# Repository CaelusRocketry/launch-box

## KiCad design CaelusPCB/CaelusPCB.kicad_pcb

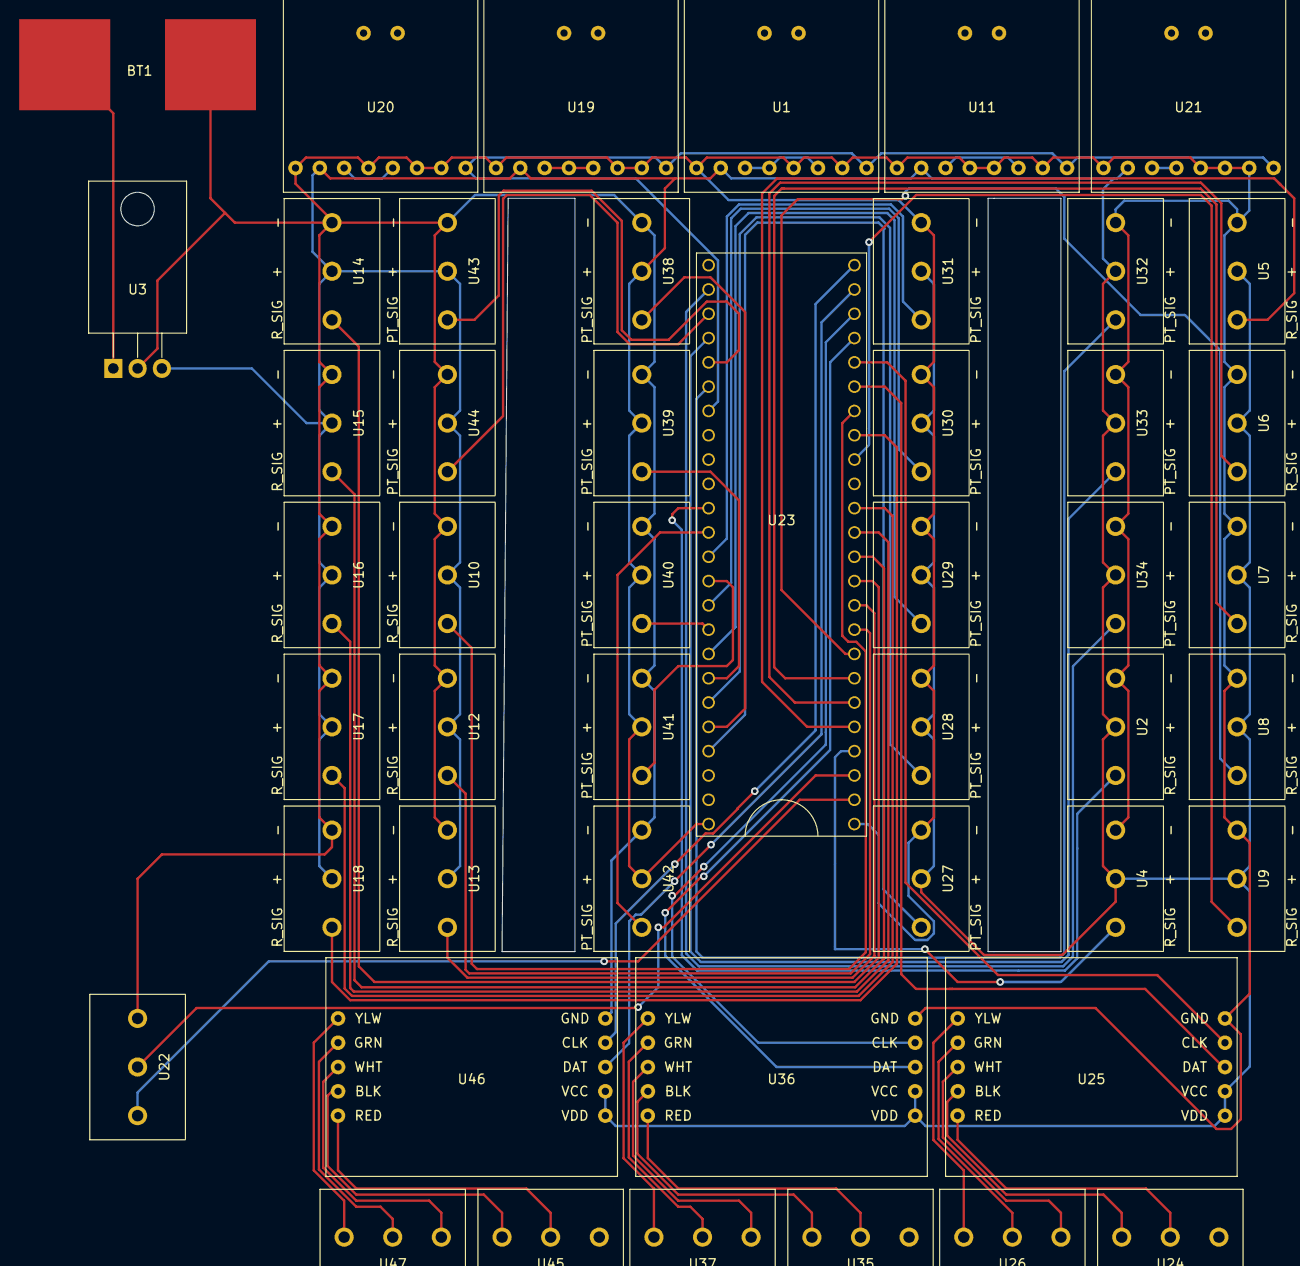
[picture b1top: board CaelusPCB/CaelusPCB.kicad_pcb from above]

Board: 2 copper layers, 48 parts (0 on the bottom side), 62 nets.

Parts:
BT1: Battery_Cell; Lipo_Battery_Connector
U1, U11, U19, U20, U21: MAX31850
U2, U4, U5, U6, U7, U8, U9, U10, U12, U13, U14, U15, U16, U17, U18, U22, U24, U26, U27, U28, U29, U30, U31, U32, U33, U34, U35, U37, U38, U39, U40, U41, U42, U43, U44, U45, U47: SerialScrewTerminals; ScrewTerminals
U3: L7805; TO-220-3_Horizontal_TabDown
U23: Teensy3.6; Teensy 3.6
U25, U36, U46: LoadCellAmp

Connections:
1: U2.1, U23.13
2: U4.1, U23.2
3: U5.1, U23.3
4: U6.1, U23.4
5: U7.1, U23.5
6: U8.1, U23.6
7: U12.1, U23.7
8: U13.1, U23.8
9: U14.1, U23.9
10: U15.1, U23.10
11: U16.1, U23.11
12: U17.1, U23.12
13: U9.1, U23.24
14: U18.1, U23.25
15: U10.1, U23.26
16: U23.27, U25.8
17: U23.28, U25.7
18: U23.29, U36.8
19: U23.30, U36.7
20: U23.31, U46.8
21: U23.32, U46.7
22: U1.8, U11.8, U19.8, U20.8, U21.8, U23.39
23: U22.1, U23.0
24: U22.2, U23.1
+5V: U1.2, U2.2, U3.3, U4.2, U5.2, U6.2, U7.2, U8.2, U9.2, U10.2, U11.2, U12.2, U13.2, U14.2, U15.2, U16.2, U17.2, U18.2, U19.2, U20.2, U21.2, U23.40, U25.9, U25.10, U27.2, U28.2, U29.2, U30.2, U31.2, U32.2, U33.2, U34.2, U36.9, U36.10, U38.2, U39.2, U40.2, U41.2, U42.2, U43.2, U44.2, U46.9, U46.10
GND1: BT1.2, U1.1, U1.5, U1.7, U2.3, U3.2, U4.3, U5.3, U6.3, U7.3, U8.3, U9.3, U10.3, U11.1, U11.4, U11.5, U11.7, U12.3, U13.3, U14.3, U15.3, U16.3, U17.3, U18.3, U19.1, U19.6, U19.7, U20.1, U20.4, U20.6, U20.7, U21.1, U21.5, U21.6, U21.7, U22.3, U23.46, U25.6, U27.3, U28.3, U29.3, U30.3, U31.3, U32.3, U33.3, U34.3, U36.6, U38.3, U39.3, U40.3, U41.3, U42.3, U43.3, U44.3, U46.6
unnamed: BT1.1, U3.1
unnamed: U1.3, U1.4, U1.6
unnamed: U11.3, U11.6
unnamed: U19.3, U19.4, U19.5
unnamed: U20.3, U20.5
unnamed: U21.3, U21.4
unnamed: U23.14, U42.1
unnamed: U23.15, U31.1
unnamed: U23.16, U41.1
unnamed: U23.17, U30.1
unnamed: U23.18, U40.1
unnamed: U23.19, U29.1
unnamed: U23.20, U39.1
unnamed: U23.21, U28.1
unnamed: U23.22, U38.1
unnamed: U23.23, U27.1
unnamed: U23.34, U34.1
unnamed: U23.35, U44.1
unnamed: U23.36, U33.1
unnamed: U23.37, U43.1
unnamed: U23.38, U32.1
unnamed: U24.1, U25.4
unnamed: U24.2, U25.5
unnamed: U25.1, U26.1
unnamed: U25.2, U26.2
unnamed: U25.3, U26.3
unnamed: U35.1, U36.4
unnamed: U35.2, U36.5
unnamed: U36.1, U37.1
unnamed: U36.2, U37.2
unnamed: U36.3, U37.3
unnamed: U45.1, U46.4
unnamed: U45.2, U46.5
unnamed: U46.1, U47.1
unnamed: U46.2, U47.2
unnamed: U46.3, U47.3

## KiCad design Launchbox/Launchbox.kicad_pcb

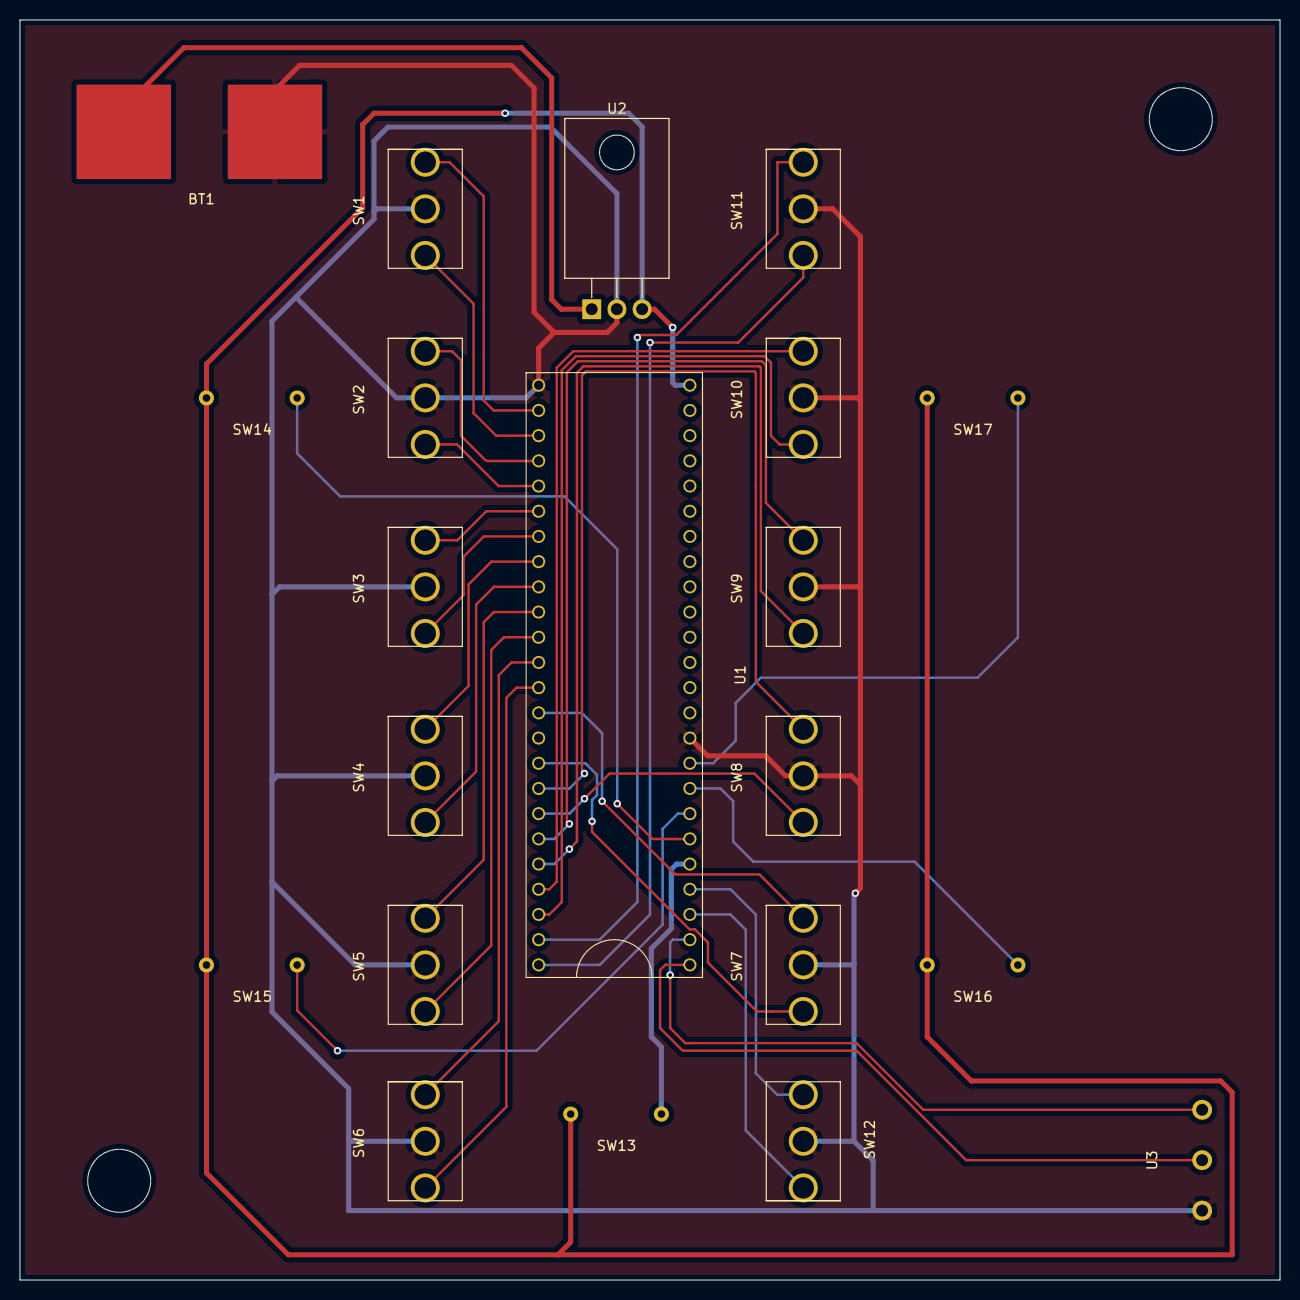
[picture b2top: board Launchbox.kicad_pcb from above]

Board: 2 copper layers, 127.0 x 127.0 mm, 21 parts (0 on the bottom side), 34 nets.

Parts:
BT1: Battery_Cell; Lipo_Battery_Connector
SW1, SW2, SW3, SW4, SW5, SW6, SW7, SW8, SW9, SW10, SW11, SW12: SW_SPDT_MSM; SPDT_Slide_Switch
SW13, SW14, SW15, SW16, SW17: SW_Push; Pushbutton
U1: Teensy3.6; Teensy 3.6
U2: L7805; TO-220F-3_Horizontal_TabDown
U3: SerialScrewTerminals; ScrewTerminals

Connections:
GND: BT1.2, SW1.2, SW2.2, SW3.2, SW4.2, SW5.2, SW6.2, SW7.2, SW8.2, SW9.2, SW10.2, SW11.2, SW12.2, U1.43, U1.46, U2.2, U3.3
unnamed: BT1.1, U2.1
unnamed: SW1.1, U1.0
unnamed: SW1.3, U1.1
unnamed: SW2.1, U1.2
unnamed: SW2.3, U1.3
unnamed: SW3.1, U1.4
unnamed: SW3.3, U1.5
unnamed: SW4.1, U1.6
unnamed: SW4.3, U1.7
unnamed: SW5.1, U1.8
unnamed: SW5.3, U1.9
unnamed: SW6.1, U1.10
unnamed: SW6.3, U1.11
unnamed: SW7.1, U1.12
unnamed: SW7.3, U1.24
unnamed: SW8.1, U1.25
unnamed: SW8.3, U1.26
unnamed: SW9.1, U1.27
unnamed: SW9.3, U1.28
unnamed: SW10.1, U1.29
unnamed: SW10.3, U1.30
unnamed: SW11.1, U1.31
unnamed: SW11.3, U1.32
unnamed: SW12.1, U1.35
unnamed: SW12.3, U1.36
unnamed: SW13.1, SW14.1, SW15.1, SW16.1, SW17.1, U1.40, U2.3
unnamed: SW13.2, U1.37
unnamed: SW14.2, U1.38
unnamed: SW15.2, U1.39
unnamed: SW16.2, U1.45
unnamed: SW17.2, U1.44
unnamed: U1.33, U3.2
unnamed: U1.34, U3.1

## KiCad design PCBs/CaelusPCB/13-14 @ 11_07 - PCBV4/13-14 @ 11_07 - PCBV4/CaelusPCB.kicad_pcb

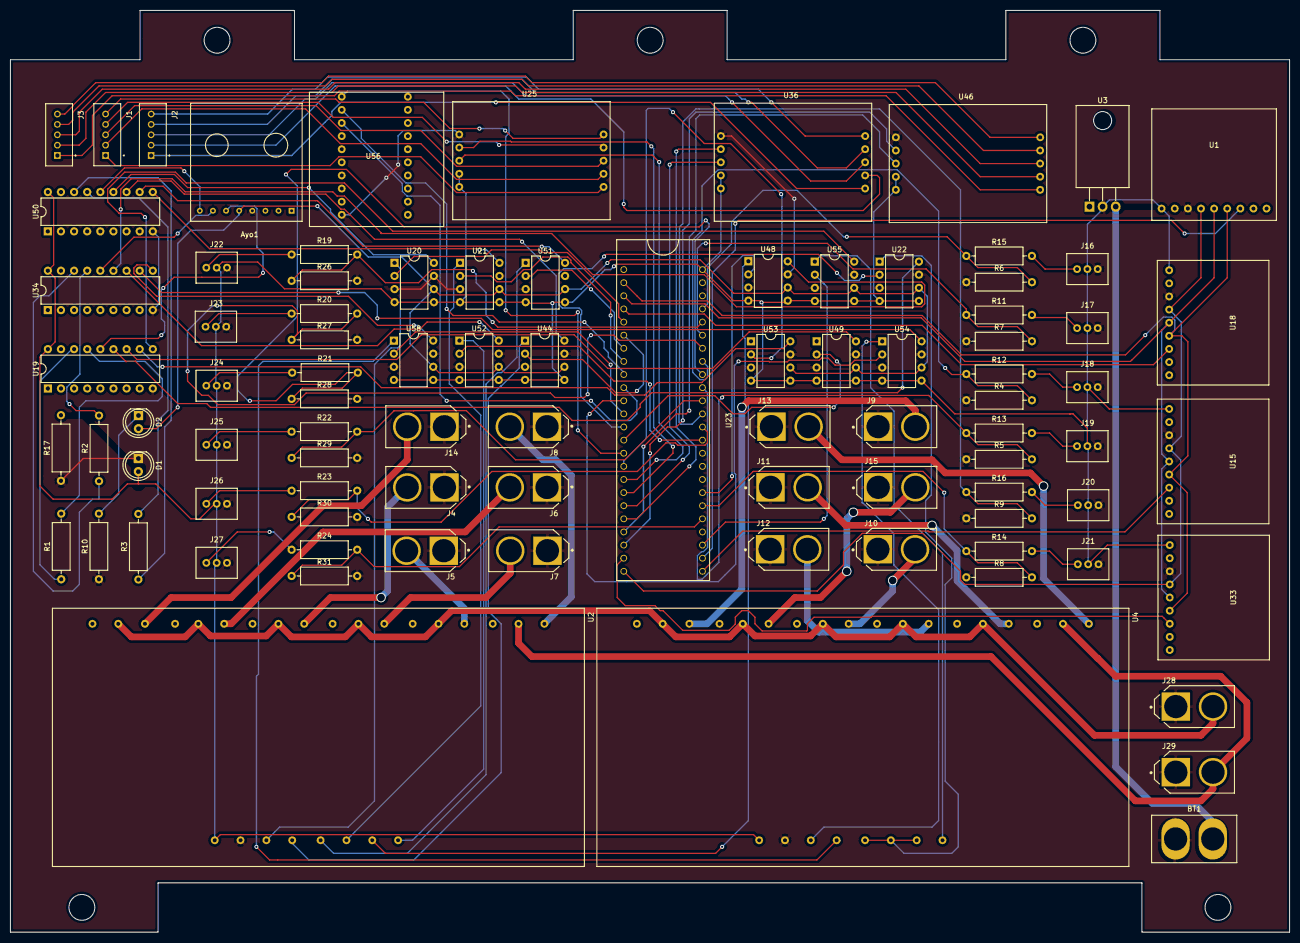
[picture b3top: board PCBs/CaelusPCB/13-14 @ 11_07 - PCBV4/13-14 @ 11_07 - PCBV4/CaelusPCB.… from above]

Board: 2 copper layers, 247.7 x 178.4 mm, 89 parts (0 on the bottom side), 118 nets.

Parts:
Ayo1: RJ45EthernetBreakout
BT1: Battery_Cell; XT60H-M12
D1, D2: LED; LED_D5.0mm
J1, J2, J3: 440055-5; TE_1735446-5
J4, J5, J6, J7, J8, J9, J10, J11, J12, J13, J14, J15: XT60-M; AMASS_XT60-M
J16, J17, J18, J19, J20, J21, J22, J23, J24, J25, J26, J27: 440055-3; Crimp_Header
J28, J29: CaelusPCB-rescue_XT60-M-CaelusPCB; AMASS_XT60-M
R1, R2, R3, R4, R5, R6, R7, R8, R9, R11, R12, R13, R14, R15, R16, R19, R20, R21, R22, R23, R24, R26, R27, R28, R29, R30, R31: R_US; R_Axial_DIN0309_L9.0mm_D3.2mm_P12.70mm_Horizontal
R10, R17: R; R_Axial_DIN0309_L9.0mm_D3.2mm_P12.70mm_Horizontal
U1, U15, U18, U33: MAX31856
U2, U4: 6-Channel-5V-Relays; 6x_relay_module
U3: LD1085V50; TO-220-3_Horizontal_TabDown
U19, U34, U50: Launchbox_HT12D; DIP-18_W7.62mm
U20, U21, U22, U44, U48, U49, U51, U52, U53, U54, U55, U58: SPDT_IC; DIP-8_W7.62mm
U23: Teensy3.6; Teensy 3.6
U25, U36, U46: LoadCellAmp
U56: XBee_Breakout; Xbee_Breakout

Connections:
1: U1.4, U15.4, U18.4, U23.32, U33.4
2: U23.31, U33.7
3: U20.2, U23.3
3.3: U23.47, U56.1
4: U23.4, U44.2
5: U23.5, U51.2
6: U21.2, U23.6
7: U23.39, U48.2
8: U23.13, U52.2
9: U23.9, U54.2
10: U23.10, U58.2
11: U22.2, U23.11
12: U23.12, U49.2
13: U1.6, U15.6, U18.6, U23.0, U33.6
14: U1.5, U15.5, U18.5, U23.1, U33.5
15: U18.7, U23.2
16: U23.25, U25.8
17: U23.26, U25.7
18: U23.27, U36.8
19: U23.28, U36.7
20: U23.29, U46.8
21: U23.30, U46.7
25: Ayo1.8, U50.14
26: Ayo1.7, U34.14
27: Ayo1.6, U19.14
28: U20.8, U50.13
29: U44.8, U50.12
30: U50.11, U51.8
31: U21.8, U50.10
32: U34.13, U48.8
33: U34.12, U52.8
34: U34.11, U54.8
35: U34.10, U58.8
36: U19.13, U22.8
37: U19.12, U49.8
38: U19.11, U53.8
39: U19.10, U55.8
40: U2.3, U20.1
41: U2.4, U44.1
42: U2.5, U51.1
43: U2.6, U21.1
44: U2.7, U48.1
45: U2.8, U52.1
46: U4.3, U54.1
47: U4.4, U58.1
48: U4.5, U4.6, U4.7, U22.1
50: U15.7, U23.33
51: U1.7, U23.34
52: Ayo1.5, D2.2, U20.6, U21.6, U22.6, U44.6, U48.6, U49.6, U51.6, U52.6, U53.6, U54.6, U55.6, U58.6
54: U4.8, U55.1
57: U23.24, U53.2
58: U23.35, U55.2
60: U23.8, U56.3
61: U23.7, U56.2
62: J4.2, U2.17
63: J7.2, U2.20
64: J5.2, U2.23
65: J8.2, U2.26
66: J9.2, U4.11
67: J15.2, U4.14
68: J10.2, U4.17
69: J12.2, U4.20
70: J11.2, U4.23
71: J13.2, U4.26
80: J14.2, U2.11
81: J6.2, U2.14
+5V: D1.2, J16.2, J17.2, J18.2, J19.2, J20.2, J21.2, J22.2, J23.2, J24.2, J25.2, J26.2, J27.2, U1.1, U2.1, U3.2, U4.1, U15.1, U18.1, U19.18, U20.4, U20.5, U21.4, U21.5, U22.4, U22.5, U23.40, U25.9, U25.10, U33.1, U34.18, U36.9, U36.10, U44.4, U44.5, U46.9, U46.10, U48.4, U48.5, U49.4, U49.5, U50.18, U51.4, U51.5, U52.4, U52.5, U53.4, U53.5, U54.4, U54.5, U55.4, U55.5, U58.4, U58.5
+12V: J28.2, U2.10, U2.13, U2.16, U2.19, U2.22, U4.10, U4.13, U4.16, U4.19, U4.22
+24V: J29.2, U2.25, U4.25
GND1: Ayo1.4, BT1.2, J4.1, J5.1, J6.1, J7.1, J8.1, J9.1, J10.1, J11.1, J12.1, J13.1, J14.1, J15.1, J16.3, J17.3, J18.3, J19.3, J20.3, J21.3, J22.3, J23.3, J24.3, J25.3, J26.3, J27.3, J28.1, J29.1, R4.1, R5.1, R6.1, R7.1, R8.1, R9.1, R10.1, R17.2, R26.2, R27.2, R28.2, R29.2, R30.2, R31.2, U1.3, U2.2, U3.1, U4.2, U15.3, U18.3, U19.9, U20.3, U20.7, U21.3, U21.7, U22.3, U22.7, U23.46, U25.6, U33.3, U34.9, U36.6, U44.3, U44.7, U46.6, U48.3, U48.7, U49.3, U49.7, U50.9, U51.3, U51.7, U52.3, U52.7, U53.3, U53.7, U54.3, U54.7, U55.3, U55.7, U56.10, U58.3, U58.7
unnamed: BT1.1, U3.3
unnamed: D1.1, R17.1
unnamed: D2.1, R10.2
unnamed: J1.1, U25.1
unnamed: J1.2, U25.2
unnamed: J1.3, U25.3
unnamed: J1.4, U25.4
unnamed: J1.5, U25.5
unnamed: J2.1, U36.1
unnamed: J2.2, U36.2
unnamed: J2.3, U36.3
unnamed: J2.4, U36.4
unnamed: J2.5, U36.5
unnamed: J3.1, U46.1
unnamed: J3.2, U46.2
unnamed: J3.3, U46.3
unnamed: J3.4, U46.4
unnamed: J3.5, U46.5
unnamed: J16.1, R15.2
unnamed: J17.1, R11.2
unnamed: J18.1, R12.2
unnamed: J19.1, R13.2
unnamed: J20.1, R16.2
unnamed: J21.1, R14.2
unnamed: J22.1, R19.1
unnamed: J23.1, R20.1
unnamed: J24.1, R21.1
unnamed: J25.1, R22.1
unnamed: J26.1, R23.1
unnamed: J27.1, R24.1
unnamed: R1.1, U19.16
unnamed: R1.2, U19.15
unnamed: R2.1, U34.16
unnamed: R2.2, U34.15
unnamed: R3.1, U50.16
unnamed: R3.2, U50.15
unnamed: R7.2, R11.1, U23.21
unnamed: R4.2, R12.1, U23.19
unnamed: R5.2, R13.1, U23.17
unnamed: R8.2, R14.1, U23.38
unnamed: R6.2, R15.1, U23.23
unnamed: R9.2, R16.1, U23.15
unnamed: R19.2, R26.1, U23.22
unnamed: R20.2, R27.1, U23.20
unnamed: R21.2, R28.1, U23.18
unnamed: R22.2, R29.1, U23.16
unnamed: R23.2, R30.1, U23.14
unnamed: R24.2, R31.1, U23.37
